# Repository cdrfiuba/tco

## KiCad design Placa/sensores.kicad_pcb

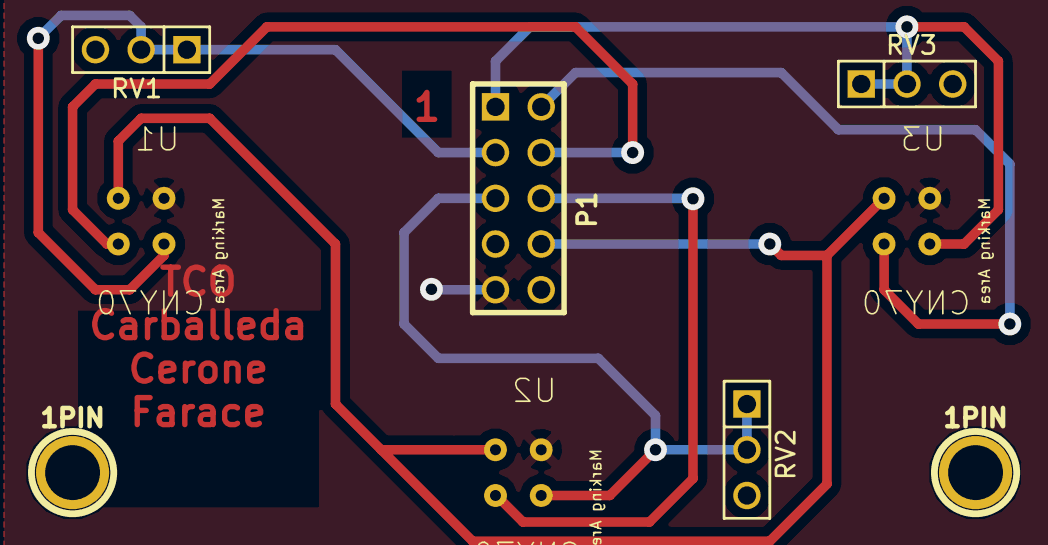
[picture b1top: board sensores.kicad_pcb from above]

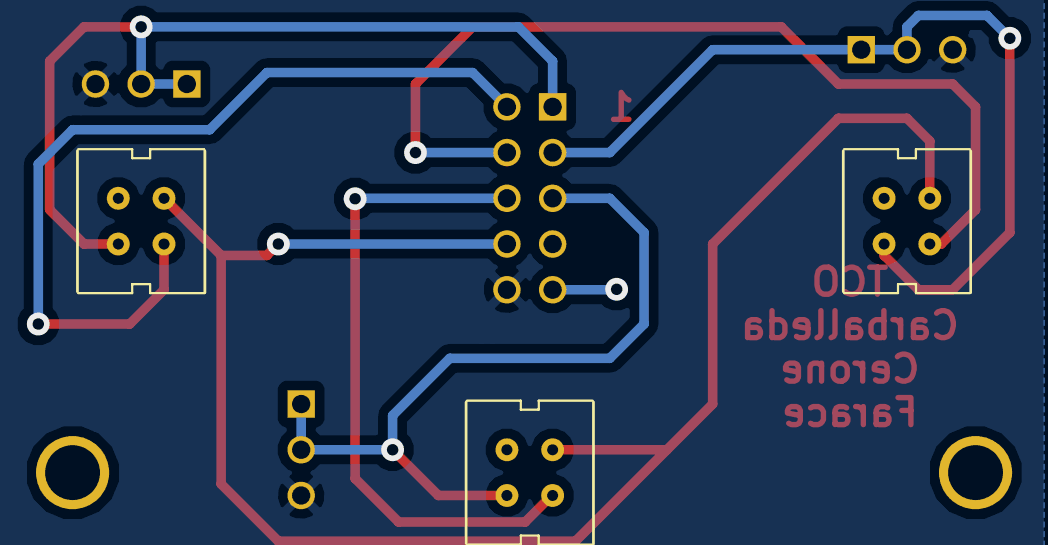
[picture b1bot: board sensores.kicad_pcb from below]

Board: 2 copper layers, 9 parts (3 on the bottom side), 9 nets.

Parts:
1PIN, 1PIN#2: P***; 1pin
P1: CONN_5X2; PIN_ARRAY_5x2
RV1, RV2, RV3: POT; PIN_ARRAY_3X1
U1, U2, U3: CNY70; cny70-4

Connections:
/5V: P1.9, U1.C, U2.C, U3.C
/GND: P1.10, RV1.3, RV2.3, RV3.3
/GND LED sensores: P1.8, U1.K, U2.K, U3.K
/PA0 - Sensor piso izquierda: P1.3, RV1.1, RV1.2, U1.E
/PA1 - Sensor piso centro: P1.5, RV2.1, RV2.2, U2.E
/PA2 - Sensor piso derecha: P1.1, RV3.1, RV3.2, U3.E
/Vcc sensor piso centro: P1.6, U2.A
/Vcc sensor piso derecha: P1.2, U3.A
/Vcc sensor piso izquierda: P1.4, U1.A

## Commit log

2013-04-14 Subo archivos: Esquematico de sensores de piso (Kicad) y Primera aproximacion a su ubicacion (Dia)
2013-04-25 comienzo informe.
2013-04-26 remuevo carpeta.
2013-04-26 añado digramas de flujo.
2013-04-26 agrego los archivos de diseño modificados a carpeta "dia" , dentro de informe
2013-04-28 Agrego archivos nuevos. Placa microcontrolador terminada Proyecto kicad todas las placas Algunos datasheet Algunas imagenes Documentos anteproyecto
2013-04-28 agrego exports para crear PCB
2013-04-29 Agrego cambios en la placa microcontrolador, propuestos por Joaco:
    1) Agrego filtro para los AD
    2) Agrego resistencias para cada led de los sensores
    3) Hice algo mas pero no recuerdo que.
2013-04-29 Ahora si, hice un update de la última version del repo y subo los cambios.
2013-04-29 Agrego carpeta gerber con los archivos necesarios para gabricar PCB
2013-04-30 Termino PCB motores. Agrego biblioteca LMD18200. Agrego el anteproyecto hecho por Gisela.
2013-04-30 Ahora si, agrego los archivos, me había olvidado del Add.
2013-05-02 renuevo gerbers
2013-05-02 agrego los ps necesarios para PCB
2013-05-02 invierto colores en .ps
2013-05-19 agrego gerbers de motores
2013-05-20 invierto .ps
2013-05-22 trabajo en sensores
2013-05-25 Agrego archivos placa potencia. Agrego biblioteca ptn78020w.
2013-05-25 trabajo en Sensores de piso
2013-05-25 cambio en sensores.pro
2013-05-26 Agrego alimentación.brd, placa donde se va a montar motores/sensores/baterías.
2013-05-26 arreglo placa sensores
2013-05-27 Termino y ruteo placa Sensores, Creo Gerbers de Placa de sensores y de Alimentacion.
2013-05-27 agrego Gerbers de Sensores
2013-05-27 Agrego codigo que usa interrupciones atmega88
2013-05-27 reemplazo un gerber que estaba fuera de cuadro.
2013-05-29 hago pwm
2013-05-30 agrego carpeta con Makefile y pwm.c
2013-05-31 Agrego Make funcionando para atmega16. Agrego serie.c función que utiliza la interrupción de puerto serie para hacer un ECHO. Probado y funcionando. Agrego hgignore y lo modifico para no versionar ar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
2013-06-01 Agrego PWM funcionando. Falta hacer el codigo más prolijo.
2013-06-02 Agrego archivo "encoders.c" : se inicializan y configuran los timers 0 y 2. Modifico "pwm.c": emprolijo codigo
2013-06-02 Agrego archivos placa motor Rev:2.0 Agrego un intento de ir juntando todo en un solo lugar. Todavía falta.
2013-06-02 Agrego funciones manejo de motores.
2013-06-02 modifico pwm.c
2013-06-02 Completo funciones manejo de motores. Todavía falta hacer algunos retoques.
2013-06-02 Agrego función para enviar una cadena de caracteres por el puerto serie. Modifico interrupción del puerto serie para cargar los datos recibidos en un string. Si se reciben más datos que la longitud d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
2013-06-02 Funcion para sensores de pared
2013-06-03 agrego funcion avanzar_celda() en motores.c
2013-06-03 agrego algoritmo para los sensores del piso.
2013-06-03 arreglo algo en motores.c (cambio una comparacion en funcion avanzar_celda )
2013-06-03 Cambio nombre de algunas carpetas, tenian espacios y era molesto para trabajar con la consola. Modifico funciones manejo sensores de distancia. Todavía no esta terminada, lo agrego a modo de referenc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
2013-06-03 Me olvidé de agregar los archivos.
2013-06-03 agrego carpeta donde hago codigo para velocista, cambio funcion avanzar_celda
2013-06-04 Borro carpeta con espacio.
2013-06-05 Agrego prueba rapida para medición sensor distancia pared.
2013-06-06 Agrego prueba rapido medicion distancia.
2013-06-06 Midiendo distancia pared y enviandola por serie.
2013-06-06 Prueba sensor distancia. Tenemos un problema que se queda colgado el sensor y hay que volver a hacer un trigger para sacarlo de ese estado.
2013-06-06 Algunos arreglos, no se si va andar.
2013-06-06 Algunos cambios más, a ver si esta más cerca
2013-06-06 Subo lo último que tengo. Midiendo distancia pared. Cuando mide distancias grandes (mayor a 30 cm) se cuelga.
2013-06-06 Ahora si, borre los archivos que estaban molestando.
2013-06-06 agrego carpeta con pruebas para encoder
2013-06-06 Agrego cambios funciones en prueba para agregar los encoders. No funciona.
2013-06-06 Agrego modificiaciones al codigo tco/Source/programa
    Mide distancia en forma estable.
    Corregí el tipo de las variables.
2013-06-06 Hice la documentacion para la compentencia. Ademas arregle en el Kicad el reset del micro.
2013-06-06 Funcionan los 3 sensores de pared.
2013-06-06 Agrego funcion mantener distancia, compila.
2013-06-07 Primera prueba de TCO en movimiento. Trando de mantener una distancia fija.
2013-06-08 Avances parciales, agregamos rotar 90°. Agregamos un pequeño algoritmo, pero no funciona.
2013-06-08 Intento de codigo medio cabeza
2013-06-08 Conjunto de cambios retirado: f4b842901451
2013-06-08 Recorre el laberinto maso menos muy cabeza
2013-06-08 Intento de resolverdor, resulve el laberinto girando a la derecha. Falta resolver error al moverse.
2013-06-08 Creemos que funciona. Hay que empezar a hacer pruebas y poner la corrección de rumbo.
2013-06-08 Va saliendo. Gira a izquierda retrocediendoVa saliendo.
2013-06-08 comit por las dudas
2013-06-08 cambiamos cables , sensores por separado
2013-06-10 Somos felices! Los sensores de distancia no se cuelgan.
2013-06-11 Intentado hacer funcinar los encoders, posible error de configuracion, el Timer2 cuenta cuando no deberia.
2013-06-11 Agrego algunas imagenes para el wiki.
2013-06-11 Hago un merge a mano entre la versión que recorrió el laberinto en la competencia Megaman y la que tiene solucionado el problema de los sensores. Hice un make y compila, de todas formas hay que proba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
    Borré archivos que creo no se estan usando. De todas formas, esta todo versionado.
2013-06-11 Placa microcontrolador revisión 2. Agrego modificaciones: posibildad de encender todos los sensores desde el micro. Identificar interrupción de cada sensor.
2013-06-11 Me olvidé de agregar los LED's indicadores.
2013-06-11 Agrego retoques en 2da revisión PCB micro
2013-06-12 Se agrega PCB placa micros revisión 2.
2013-06-12 Se agrandan los agujeros de la placa para que los componentes entren mejor.
2013-06-12 Modificación placas 2da revisión.
    Placa microcontrolador: Se terminó el PCB. Se agrandaron los agujeros. Se agregó texto. Ya esta lista para fabricar.
    Placa motores: Se agregó texto para tener referencia y evitar que salga al revés.
    Placa alimentación: Se tomaron las mediciones para poner las placas anterior correctamente. Falta terminar el PCB.
2013-06-12 Funcion para los sensores de piso
2013-06-12 Funciona bien, con la modificacion de la medición de pared. Con esto hubieramos ganado la competencia.
2013-06-12 guardo por las dudas
2013-06-13 Se esta midiendo distancia utilizando el mismo timer que el PWM. De esta forma nos ahorramos un timer para poder utilizar los encoders.
2013-06-13 Pruebas con los encoders. Todavía no funciona,
2013-06-13 Agrego esquematico versión 1 PCB micro para poder usar de referencia hasta que fabriquemos la segunda placa.
2013-06-13 Avances medición del piso. No wanda nara.
2013-06-13 Codigo con sensores de piso funcionando.
2013-06-15 Encoder rueda derecha funciona OK. Vamos por la izquierda!
2013-06-15 Agrego configuración timer 2 para poder contar encoder. Pero no funciona.
2013-06-15 Se hacen avances en la utilizacion del encoder. Rueda derecha funciona ok. Se utiliza la interrupción por overflow para sumar más distancia.
    Rueda izquierda configurada, pero no anda como corresponde.
2013-06-15 Prueba para ver los valores de los dos encoders a través del puerto serie. No funciona el encoder de la rueda izquierda
2013-06-18 Se hacen pruebas para usar el encoder de la rueda izquierda sin el timer, solo mirando el estado del puerto. No funciona.
2013-06-18 Funciona el encoder de la rueda izquierda viendo todo el tiempo el estado del puerto. De todas formas da muy distinto que la rueda derecha con el timer (482 pulsos contra 272). Hay que probar con la 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
2013-06-18 Funcionan los dos encoders! La rueda derecha por un contador en T0 y la rueda izquierda por interrupción.
2013-06-18 Mejorando la función que rota a la derecha e izquierda. Seguramente haya que cambiar la cantidad de pulsos que rota.
2013-06-18 Algunos avances, pero con problemas de medición de distancia de nuevo.
2013-06-19 Agrego avanzar con cantidad de pulsos.
2013-06-20 Avances en la corrección de sentido. Funciona bien. Falta ajustar.
2013-06-20 Ultima prueba del día. Funciona muy bien, pero falta corregir el rumbo despues del giro. Mantiene el recorrido en linea recta bastante bien, aunque falta comprar contra la pared.
2013-06-20 Se agrega una funciona que intenta corregir el rumbo. Ayuda un poco, pero hay que mejorarla.
2013-06-20 Agrego medición del piso, pero no funciona. Seguramente olvidé alguna configuración.
2013-06-20 Estaba funcionando muy bien, pero ahora mide siempre FFFF en el sensor de la derecha.
2013-06-21 Versión estable: Sale del laberinto. Falta agregar corrección de rumbo.
2013-06-21 Falta corregir rumbo.
2013-06-22 Realizó tres ciclos seguidos antes de pegarse contra la pared. La función de corrección de rumno parece qeu corrige. De todas formas todavía falta ajustar un par de cosas.
2013-06-22 Modificaciones sobre la corrección de rumbo.
2013-06-22 Se agrega carpeta para preparar CD siguiendo indicaciones página web de la materia. Se empieza informe en latex siguiendo plantilla ya armada para otro TP.
2013-06-22 Avances en el informe. Ya esta la caratula y el cuerpo. Falta agregar información.
2013-06-23 Se resolvió problema al medir el piso, otra función desactivaba la interrupción.
2013-06-24 Se detiene cuando llega a la salida. Pero no corrige bien, y hace algo raro al girar a la izquierda.
2013-06-24 Informe: Objetivos, Motivaciones, Estructura mecanica, Fotos (TCO y Laberinto)
2013-06-24 Se agregan avances en el informe.
2013-06-24 Versión final para entregar el miercoles. Se corrigieron detalles de funcionamiento. Se acomodó el código. Se probó y funciona bien.
2013-06-24 Cambio nombre informe_final. Modifico hgignore para no tomar archivos .evs
2013-06-25 edito \subsection{Identificación de color del piso} , (arreglar posibles errores de compilacion)
2013-06-25 Describo como utilizamos nuestros sensores de pared, Arreglo problema por el cual no compilaba.
2013-06-25 Se hacen algunas correcciones en el Informe.
2013-06-25 Avances del informe. Se agrega lista de materiales.
2013-06-26 Agrego diagrama de flujo del algoritmo principal que sale del laberinto. Comento linas de imagenes que agregan imagenes que no estan en /img.
2013-06-26 Correcciones del informe.
2013-06-26 Se hacen cambios en el informe. Se agrega información. Se corrige ortografia. Se agregan los esquemáticos en la carpeta del proyecto.
2013-06-26 Se agrega comunicación, y encoders. Tambien un poco de conclusiones.
2013-06-26 agrego explicacion PWM y Motores
2013-06-26 Hago algunas correcciones.
2013-06-26 Avances del informe. Se agrega parte hecha por Gisela.
2013-06-26 Agrego info a explicación sobre encoders, agrego items a software utilizado.
2013-06-26 agrego info a encoders y software utulizado
2013-06-26 Agrego versiones finales. CD listo para quemar.
2013-07-05 Se hacen correcciones en el informe. Se borran archivos innecesarios.
2013-07-05 Se hacen más correcciones en el informe.
2013-07-06 Se cargaron las versiones correctas de los esquemáticos y los PCB.
2013-07-06 Se agrega PCB para base motores.
2014-09-06 Puesta a punto
